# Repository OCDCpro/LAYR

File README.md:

With the **LAYR Open Chip Challenge**, we are creating a platform on which students themselves become drivers of innovation: We are looking for creative open-source chip designs that grow technically in several stages of the competition, address real security aspects, and are accompanied through to physical tape-out. The focus is not only on technical skills, but also on active participation in digital value chains and sovereignty - from the idea to the functional silicon solution.

## The challenge

**Link to** [LAYR 25/26: The Challenge](https://github.com/OCDCpro/LAYR/tree/main/challenge)
</p>

The LAYR challenge contains the tasks and informations to enter LAYR. Please start with reading the challenge.

## The hardware kit

**Link to** [LAYR 25/26: The hardware kit](https://github.com/OCDCpro/LAYR/tree/main/hardware_kit)
</p>

All teams will get a LAYR 25/26 hardware kit. The kits will be distributed by the teams supervisors. The link takes you to the description of the hardware kit and some additional informations about the content and the components.

**IMPORTANT:** The IDs and KEYS on the Javacards (NFC-cards) are pre-programmed by the LAYR team. A list of the cards, IDs and keys is provided with the descriptions.

## The demonstrator

**Link to** [LAYR 25/26: The demonstrator](https://github.com/OCDCpro/LAYR/tree/main/demonstrator)

## Teams submissions

**Link to** [LAYR 25/26: List of submissions](https://github.com/OCDCpro/LAYR/tree/main/submissions)
</p>

Six teams created submissions for LAYR 25/26. All of them got into production at IHP at the Tapeout in March 2026. Some of these chip designs are available in public repositories. Find them with the Link above.

## Events

**Link to** [LAYR 25/26: Events](https://github.com/OCDCpro/LAYR/tree/main/events)
</p>
LAYR hosts a series of events. 
A list of the past events with documents and materials regarding the events can be found at the link above.

#### License

Shield: [![CC BY 4.0][cc-by-shield]][cc-by]

This work is licensed under a
[Creative Commons Attribution 4.0 International License][cc-by].

[![CC BY 4.0][cc-by-image]][cc-by]

[cc-by]: http://creativecommons.org/licenses/by/4.0/
[cc-by-image]: https://i.creativecommons.org/l/by/4.0/88x31.png
[cc-by-shield]: https://img.shields.io/badge/License-CC%20BY%204.0-lightgrey.svg

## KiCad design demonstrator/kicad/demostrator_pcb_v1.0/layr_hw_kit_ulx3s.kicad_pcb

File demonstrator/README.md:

# The LAYR 25/26 demonstrator

## Description
The LAYR demonstrator is a hardware device. It brings the microchips to live and shows the functionality of the doorlock. Over the span of the LAYR 25/26 challenge the demonstrator goes through some development stages and various enhancements. 

The components of the LAYR hardware kit are used in the demonstrator to assemble a doorlock.

## Schematic V1.0

#### The schematics
[Link to Schematics as OpenOffice document](https://github.com/OCDCpro/LAYR/tree/main/demonstrator/schematic)

#### The symbols
[Link to all the single symbols from the hardware kit, as OpenOffice documents](https://github.com/OCDCpro/LAYR/tree/main/hardware_kit/pics/symbols)

## Pictures V1.0

## FPGA prototyping

#### Bitstream for ULX3S 85F FPGA board
There is a bitstream for the ULX3S 85F FPGA board available. This implementations solves all task of the LAYR 25/26 challenge. The HDL sources of the bitstream are not published yet, as they would give away a full solution for the LAYR challenge.

#### Bitstream
[Link to bitstream for ULX3S 85F FPGA](https://github.com/OCDCpro/LAYR/tree/main/demonstrator/bitstream_ulx3s)

#### Flashing the bitstream
The bitstream can be flashed to the ULX3S with the tool fujprog. For the usage, see the readme of fujprog here:

[Link to fujprog](https://github.com/kost/fujprog)

#### ULX3S pinout of the bitstream
This is an extract from the constraints file for the bitstream. It contains not only the pinout, but also additional buffer information for each pin (internal PULL UP / DOWN).

```
LOCATE COMP "rst"    SITE "R1";  # FIRE1
IOBUF  PORT "rst"    PULLMODE=DOWN IO_TYPE=LVCMOS33 DRIVE=4;

LOCATE COMP "mode"        SITE "U18"; # J2_5+  GP14
LOCATE COMP "busy"        SITE "N17"; # J2_7+  GP15
LOCATE COMP "hard_fault"  SITE "N16"; # J2_9+  GP16
LOCATE COMP "unlock"      SITE "L16"; # J2_11+ GP17
LOCATE COMP "spi_sclk"    SITE "D18"; # J2_17+ GP20
LOCATE COMP "spi_cs_1"    SITE "C18"; # J2_23+ GP21
LOCATE COMP "spi_cs_0"    SITE "B15"; # J2_25+ GP22 D15->B15
LOCATE COMP "spi_mosi"    SITE "B17"; # J2_27+ GP23
LOCATE COMP "spi_miso"    SITE "C16"; # J2_29+ GP24
LOCATE COMP "uart_txd"    SITE "D14"; # J2_31+ GP25 B15->D14
LOCATE COMP "uart_rxd"    SITE "B13"; # J2_33+ GP26
LOCATE COMP "uart_clk_in" SITE "D13"; # J2_35+ GP27
IOBUF PORT  "mode"        PULLMODE=NONE IO_TYPE=LVCMOS33 DRIVE=4;
IOBUF PORT  "busy"        PULLMODE=NONE IO_TYPE=LVCMOS33 DRIVE=4;
IOBUF PORT  "hard_fault"  PULLMODE=NONE IO_TYPE=LVCMOS33 DRIVE=4;
IOBUF PORT  "unlock"      PULLMODE=NONE IO_TYPE=LVCMOS33 DRIVE=4;
IOBUF PORT  "spi_sclk"    PULLMODE=UP IO_TYPE=LVCMOS33 DRIVE=4;
IOBUF PORT  "spi_cs_1"    PULLMODE=NONE IO_TYPE=LVCMOS33 DRIVE=4;
IOBUF PORT  "spi_cs_0"    PULLMODE=NONE IO_TYPE=LVCMOS33 DRIVE=4;
IOBUF PORT  "spi_mosi"    PULLMODE=UP IO_TYPE=LVCMOS33 DRIVE=4;
IOBUF PORT  "spi_miso"    PULLMODE=NONE IO_TYPE=LVCMOS33 DRIVE=4;
IOBUF PORT  "uart_txd"    PULLMODE=UP IO_TYPE=LVCMOS33 DRIVE=4;
IOBUF PORT  "uart_rxd"    PULLMODE=UP IO_TYPE=LVCMOS33 DRIVE=4;
IOBUF PORT  "uart_clk_in" PULLMODE=NONE IO_TYPE=LVCMOS33 DRIVE=4;
```

#### 3V3 supply with the ULX3S
The ULX3s has a built in voltage regulator for converting 5V input to 3V3. In the demonstrator with the ULX3S board, this built in regulator is used instead of the external step-down converter board. Check this in the Kicad schematics of the PCB.

## PCB

#### Kicad files
The KiCad files should open with every KiCad version >=8. There are no special libs used for symbols or footprints. Just only the standard libs for KiCad.

[Demonstrator v1.0 PCB Kicad files](https://github.com/OCDCpro/LAYR/tree/main/demonstrator/kicad/demostrator_pcb_v1.0)

[Kicad standard libs](https://www.kicad.org/libraries/download/)

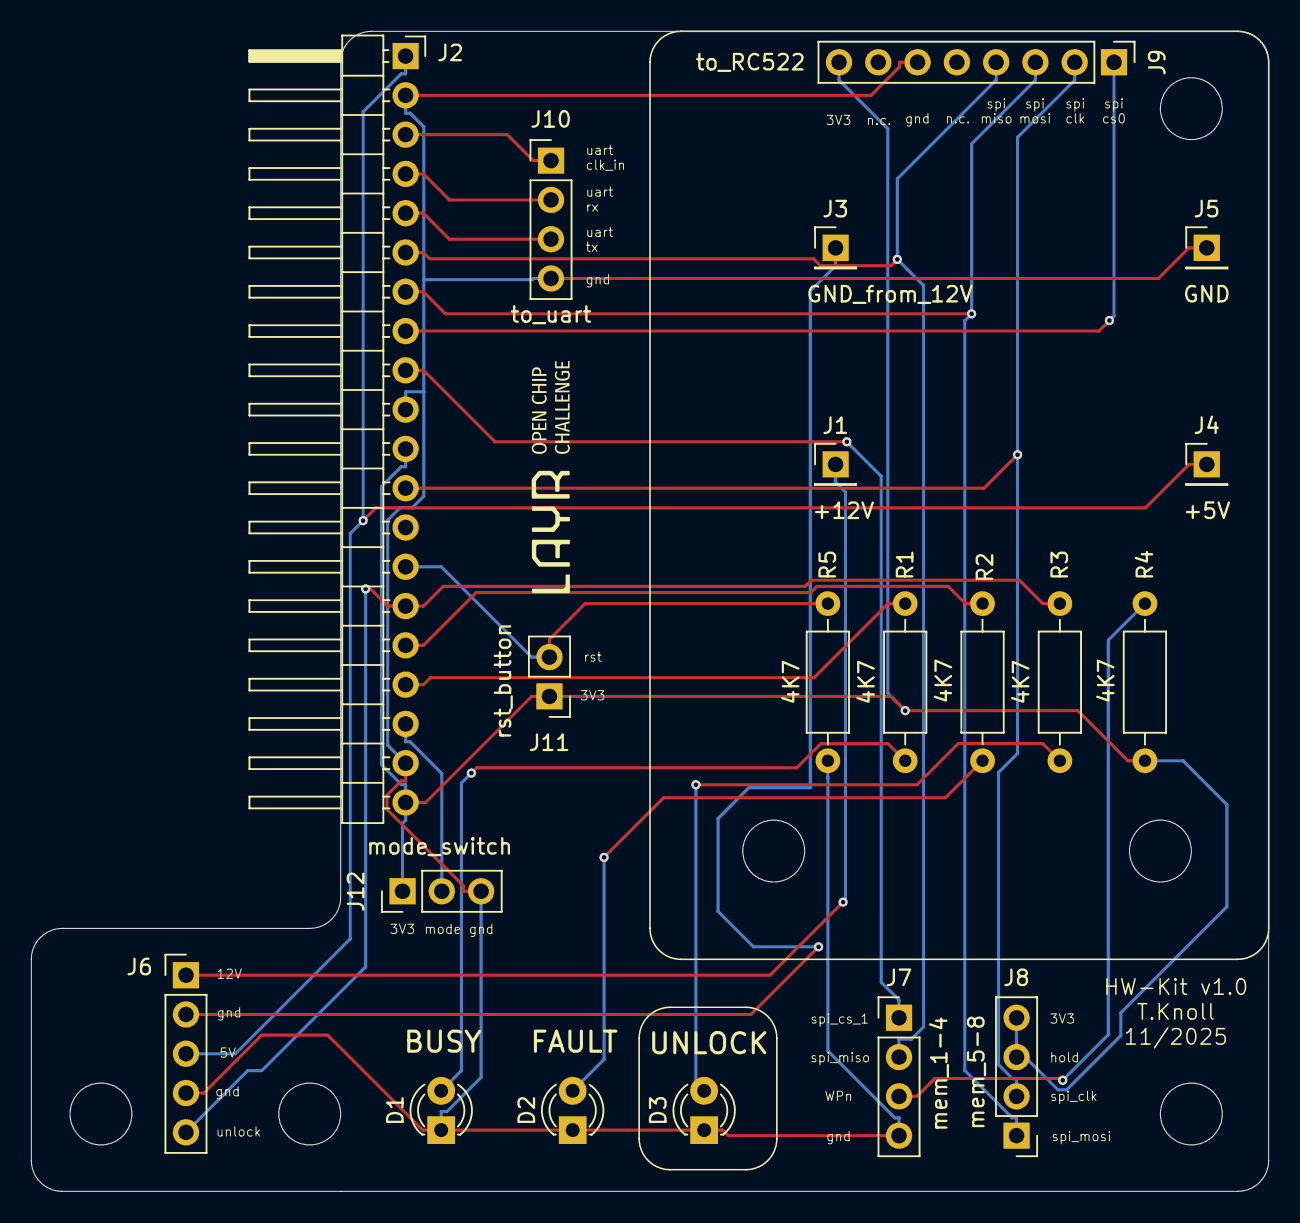
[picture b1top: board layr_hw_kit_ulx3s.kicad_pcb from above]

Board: 2 copper layers, 80.0 x 75.0 mm, 20 parts (0 on the bottom side), 22 nets.

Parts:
D1, D2, D3: LED; LED_D3.0mm
J1: +12V; PinHeader_1x01_P2.54mm_Vertical
J2: to_ULX3S; PinHeader_1x20_P2.54mm_Horizontal
J3: GND_from_12V; PinHeader_1x01_P2.54mm_Vertical
J4: +5V; PinHeader_1x01_P2.54mm_Vertical
J5: GND; PinHeader_1x01_P2.54mm_Vertical
J6: to_lock; PinHeader_1x05_P2.54mm_Vertical
J7: mem_1-4; PinHeader_1x04_P2.54mm_Vertical
J8: mem_5-8; PinHeader_1x04_P2.54mm_Vertical
J9: to_RC522; PinHeader_1x08_P2.54mm_Vertical
J10: to_uart; PinHeader_1x04_P2.54mm_Vertical
J11: rst_button; PinHeader_1x02_P2.54mm_Vertical
J12: mode_switch; PinHeader_1x03_P2.54mm_Vertical
R1, R2, R3, R4, R5: 4K7; R_Axial_DIN0207_L6.3mm_D2.5mm_P10.16mm_Horizontal

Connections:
+3V3: J2.11, J2.20, J8.3, J8.4, J9.8, J11.1, J12.1, R4.2
+5V: J2.1, J4.1, J6.3
+12V: J1.1, J6.1
/GND_12V: J3.1, J6.2
/busy: J2.17, R1.2
/hard_fault: J2.16, R2.2
/mode: J2.18, J12.2
/reset: J2.14, J11.2, R5.1
/spi_cs_0: J2.8, J9.1
/spi_cs_1: J2.9, J7.1
/spi_miso: J2.6, J7.2, J9.4
/spi_mosi: J2.7, J8.1, J9.3
/spi_sclk: J2.12, J8.2, J9.2
/uart_clk_in: J2.3, J10.1
/uart_rxd: J2.4, J10.2
/uart_txd: J2.5, J10.3
/unlock: J2.15, J6.5, R3.2
GND: D1.1 (K), D2.1 (K), D3.1 (K), J2.2, J2.10, J2.19, J5.1, J6.4, J7.4, J9.6, J10.4, J12.3, R5.2
unnamed: D1.2 (A), R1.1
unnamed: D2.2 (A), R2.1
unnamed: D3.2 (A), R3.1
unnamed: J7.3, R4.1

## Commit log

2025-10-05 init structure and readme files
2025-10-06 del old pics
2025-10-06 merged chip specs to challenge
2025-10-06 refine of the specs, 2.2. Tapeout added
2025-10-06 structure change in chapter 2
2025-10-06 content table
2025-10-06 Add existing thoughts on security judging criteria
2025-10-06 criteria english
2025-10-06 criteria numbered list
2025-10-06 criteria 5.4+5.5 changed and english
2025-10-06 wording 5.5 changed
2025-10-06 cahnged 2.5.
2025-10-06 add CC-BY license
2025-10-06 add CC-BY link to readme
2025-10-06 5.2. higher level, more points
2025-10-06 Rename Chips_freigestellt.png to Chips_v1.png
2025-10-06 Update README.md
    Update 2.4 Tapeout Notes
2025-10-09 refined chip specs
2025-10-09 user IO pins added
2025-10-09 typo correct
2025-10-09 fixed SPI mem + nfc chip
2025-10-23 pinout changed
2025-11-06 added hw-kit
2025-11-10 Add list of keys + IDs
2025-11-12 Update README.md with LAYR Logo
2025-11-12 added hw kit pics
2025-11-12 update README with hw-kit
2025-11-12 update hw-kit pics
2025-11-13 change OCDC to LAYR in challenge
2025-11-13 clean README
2025-11-13 all english
2025-11-13 qr code stickers
2025-11-13 mem chip typo
2025-11-13 demonstrator infos
2025-11-16 kicad pics
2025-11-16 kicad repo
2025-11-19 added symbols
2025-11-19 added qr stickers for cards
2025-11-19 demostrator update
2025-11-19 hw-kit readme /w symbols
2025-11-27 datasheet links
2025-11-27 added links to schamtics and symbols docs
2025-11-27 demonst readme additions
2025-11-27 added ulx3s pinout
2025-11-27 kicad links
2025-11-27 3v3 conversion
2026-01-23 Fixed Typo MFRC522
2026-02-26 Update README.md
    Added the IHP Repository for QFN24 padframe
2026-03-08 fixed pin numbers in pinout table
2026-03-10 Minor fix to protocol specification
2026-04-06 submissions list
2026-04-06 submissions list update
2026-04-06 submission list update
2026-04-06 typo fix
2026-05-12 added events page
2026-05-12 typo
